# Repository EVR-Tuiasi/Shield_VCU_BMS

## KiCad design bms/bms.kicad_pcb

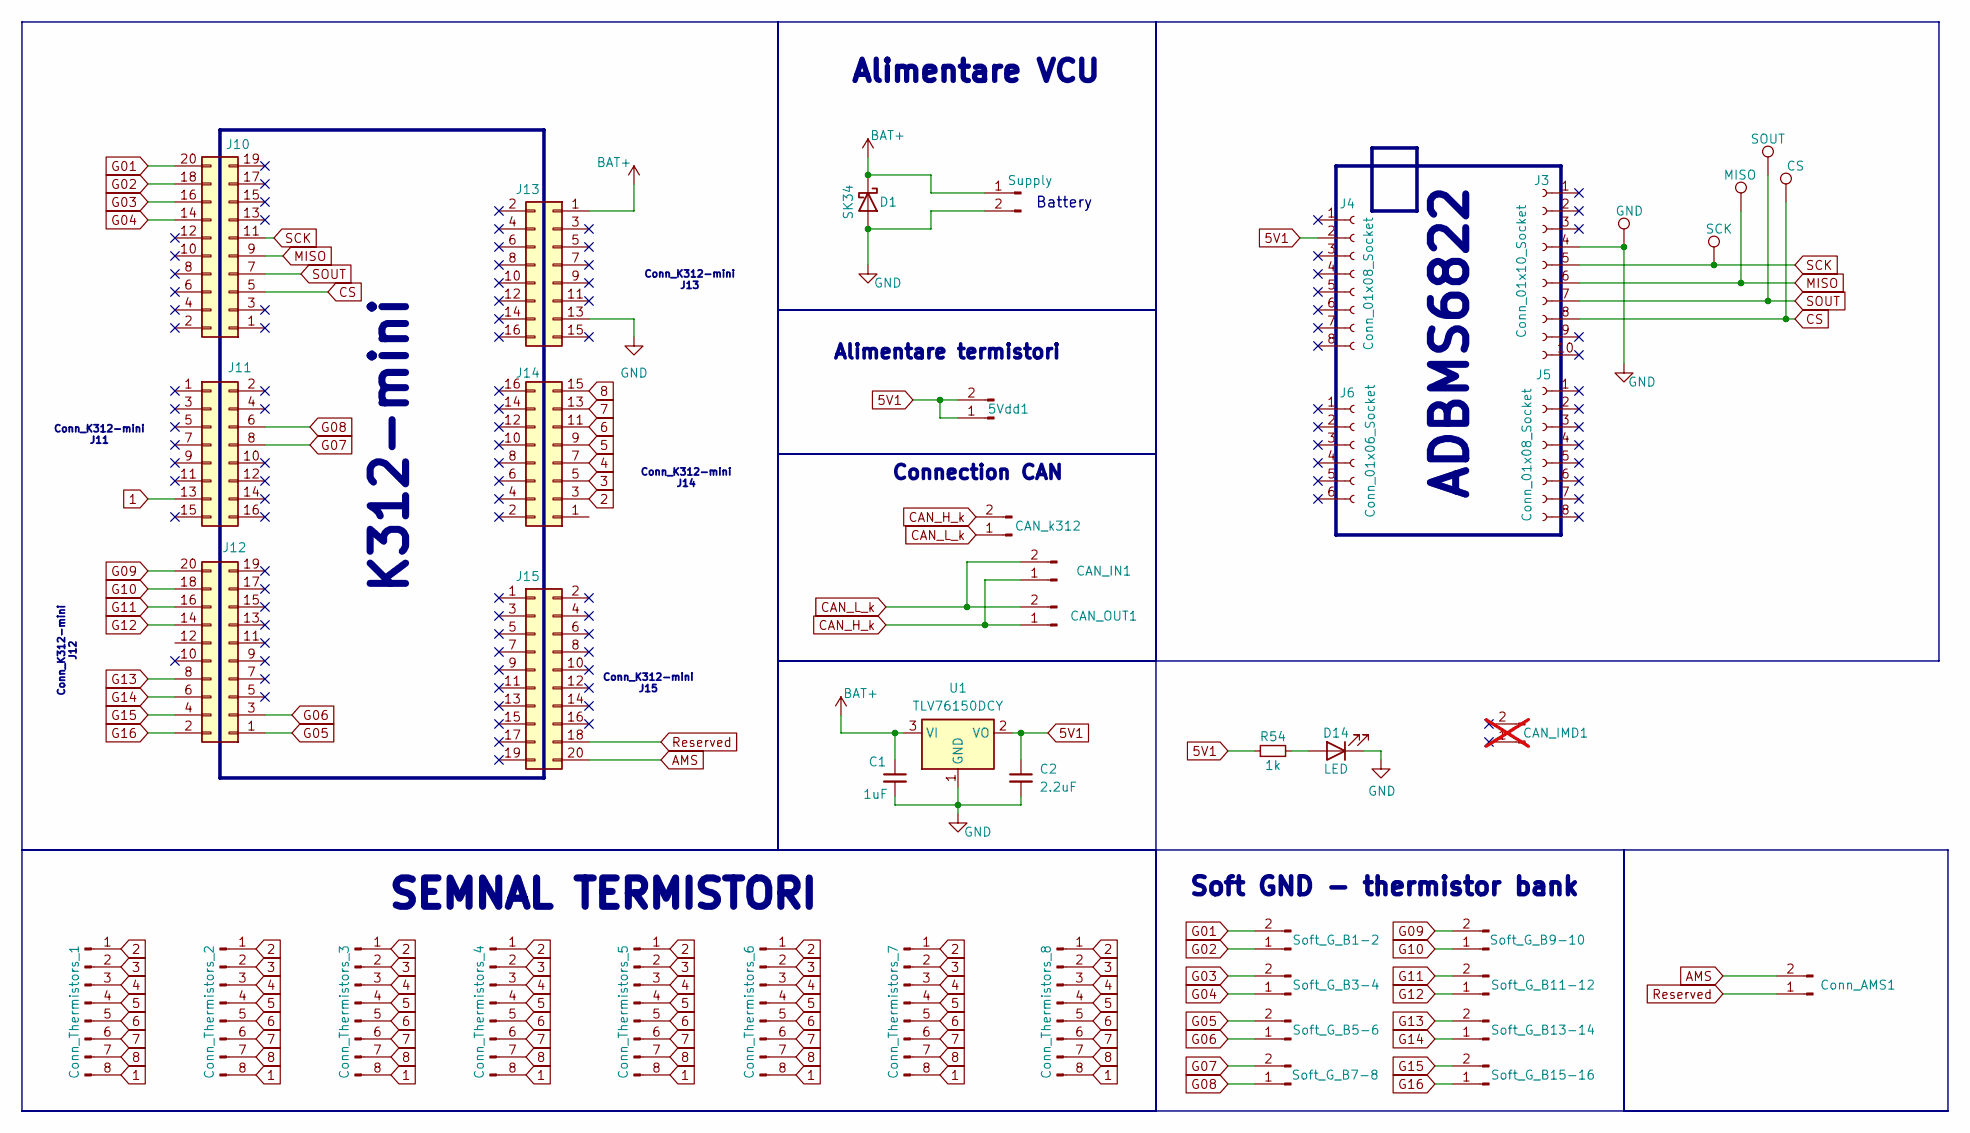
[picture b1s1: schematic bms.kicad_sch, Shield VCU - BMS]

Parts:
5Vdd1: Conn_01x02_Pin; JST_EH_B2B-EH-A_1x02_P2.50mm_Vertical
B1: Supply; JST_EH_B2B-EH-A_1x02_P2.50mm_Vertical
C1: 1uF; C_0805_2012Metric_Pad1.18x1.45mm_HandSolder
C2: 2.2uF; C_0805_2012Metric_Pad1.18x1.45mm_HandSolder
CAN_IMD1: Conn_01x02_Pin; not fitted
CAN_IN1: Conn_01x02_Pin; JST_PH_B2B-PH-K_1x02_P2.00mm_Vertical
CAN_OUT1: Conn_01x02_Pin; JST_PH_B2B-PH-K_1x02_P2.00mm_Vertical
CAN_k312: Conn_01x02_Pin; PinHeader_1x02_P2.54mm_Vertical
CS1: CS; TestPoint_Loop_D2.50mm_Drill1.0mm
Conn_AMS1: Conn_01x02_Pin; JST_EH_B2B-EH-A_1x02_P2.50mm_Vertical
Conn_Thermistors_1, Conn_Thermistors_2, Conn_Thermistors_3, Conn_Thermistors_4, Conn_Thermistors_5, Conn_Thermistors_6, Conn_Thermistors_7, Conn_Thermistors_8: Conn_01x08_Pin; JST_EH_B8B-EH-A_1x08_P2.50mm_Vertical
D1: SK34; D_SMA_Handsoldering
D14: LED; LED_0805_2012Metric
GND1: GND; TestPoint_Loop_D2.50mm_Drill1.0mm
J3: Conn_01x10_Socket; PinSocket_1x10_P2.54mm_Vertical
J4, J5: Conn_01x08_Socket; PinSocket_1x08_P2.54mm_Vertical
J6: Conn_01x06_Socket; PinSocket_1x06_P2.54mm_Vertical
J10, J12, J15: Conn_02x10_Odd_Even; PinHeader_2x10_P2.54mm_Vertical
J11, J13, J14: Conn_02x08_Odd_Even; PinHeader_2x08_P2.54mm_Vertical
MISO1: MISO; TestPoint_Loop_D2.50mm_Drill1.0mm
R54: 1k; R_1206_3216Metric_Pad1.30x1.75mm_HandSolder
SCK1: SCK; TestPoint_Loop_D2.50mm_Drill1.0mm
SOUT1: SOUT; TestPoint_Loop_D2.50mm_Drill1.0mm
Soft_G_B1-2, Soft_G_B3-4, Soft_G_B5-6, Soft_G_B7-8, Soft_G_B9-10, Soft_G_B11-12, Soft_G_B13-14, Soft_G_B15-16: Conn_01x02_Pin; JST_EH_B2B-EH-A_1x02_P2.50mm_Vertical
U1: TLV76150DCY; SOT-223-3_TabPin2

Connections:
1: Conn_Thermistors_1.8, Conn_Thermistors_2.8, Conn_Thermistors_3.8, Conn_Thermistors_4.8, Conn_Thermistors_5.8, Conn_Thermistors_6.8, Conn_Thermistors_7.8, Conn_Thermistors_8.8, J11.13
2: Conn_Thermistors_1.1, Conn_Thermistors_2.1, Conn_Thermistors_3.1, Conn_Thermistors_4.1, Conn_Thermistors_5.1, Conn_Thermistors_6.1, Conn_Thermistors_7.1, Conn_Thermistors_8.1, J14.3
3: Conn_Thermistors_1.2, Conn_Thermistors_2.2, Conn_Thermistors_3.2, Conn_Thermistors_4.2, Conn_Thermistors_5.2, Conn_Thermistors_6.2, Conn_Thermistors_7.2, Conn_Thermistors_8.2, J14.5
4: Conn_Thermistors_1.3, Conn_Thermistors_2.3, Conn_Thermistors_3.3, Conn_Thermistors_4.3, Conn_Thermistors_5.3, Conn_Thermistors_6.3, Conn_Thermistors_7.3, Conn_Thermistors_8.3, J14.7
5: Conn_Thermistors_1.4, Conn_Thermistors_2.4, Conn_Thermistors_3.4, Conn_Thermistors_4.4, Conn_Thermistors_5.4, Conn_Thermistors_6.4, Conn_Thermistors_7.4, Conn_Thermistors_8.4, J14.9
5V1: 5Vdd1.1, 5Vdd1.2, C2.1, J4.2 (Pin_2_2), R54.1, U1.2 (VO)
6: Conn_Thermistors_1.5, Conn_Thermistors_2.5, Conn_Thermistors_3.5, Conn_Thermistors_4.5, Conn_Thermistors_5.5, Conn_Thermistors_6.5, Conn_Thermistors_7.5, Conn_Thermistors_8.5, J14.11
7: Conn_Thermistors_1.6, Conn_Thermistors_2.6, Conn_Thermistors_3.6, Conn_Thermistors_4.6, Conn_Thermistors_5.6, Conn_Thermistors_6.6, Conn_Thermistors_7.6, Conn_Thermistors_8.6, J14.13
8: Conn_Thermistors_1.7, Conn_Thermistors_2.7, Conn_Thermistors_3.7, Conn_Thermistors_4.7, Conn_Thermistors_5.7, Conn_Thermistors_6.7, Conn_Thermistors_7.7, Conn_Thermistors_8.7, J14.15
AMS: Conn_AMS1.2, J15.20
BAT+: B1.1, C1.1, D1.1 (K), J13.1, U1.3 (VI)
CAN_H_k: CAN_IN1.1, CAN_OUT1.1, CAN_k312.2
CAN_L_k: CAN_IN1.2, CAN_OUT1.2, CAN_k312.1
CS: CS1.1 (1_1), J3.8, J10.5
G01: J10.20, Soft_G_B1-2.2
G02: J10.18, Soft_G_B1-2.1
G03: J10.16, Soft_G_B3-4.2
G04: J10.14, Soft_G_B3-4.1
G05: J12.1, Soft_G_B5-6.2
G06: J12.3, Soft_G_B5-6.1
G07: J11.8, Soft_G_B7-8.2
G08: J11.6, Soft_G_B7-8.1
G09: J12.20, Soft_G_B9-10.2
G10: J12.18, Soft_G_B9-10.1
G11: J12.16, Soft_G_B11-12.2
G12: J12.14, Soft_G_B11-12.1
G13: J12.8, Soft_G_B13-14.2
G14: J12.6, Soft_G_B13-14.1
G15: J12.4, Soft_G_B15-16.2
G16: J12.2, Soft_G_B15-16.1
GND: B1.2, C1.2, C2.2, D1.2 (A), D14.1 (K), GND1.1 (1_1), J3.4, J13.13, U1.1 (GND)
MISO: J3.6, J10.9, MISO1.1 (1_1)
unnamed: D14.2 (A), R54.2
Reserved: Conn_AMS1.1, J15.18
SCK: J3.5, J10.11, SCK1.1 (1_1)
SOUT: J3.7, J10.7, SOUT1.1 (1_1)

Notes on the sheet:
K312-mini
SEMNAL TERMISTORI
Soft GND - thermistor bank
Conn_K312-mini J13
Battery
Alimentare VCU
Conn_K312-mini J14
Conn_K312-mini J15
Conn_K312-mini J12
ADBMS6822
Connection CAN
Alimentare termistori
Conn_K312-mini J11

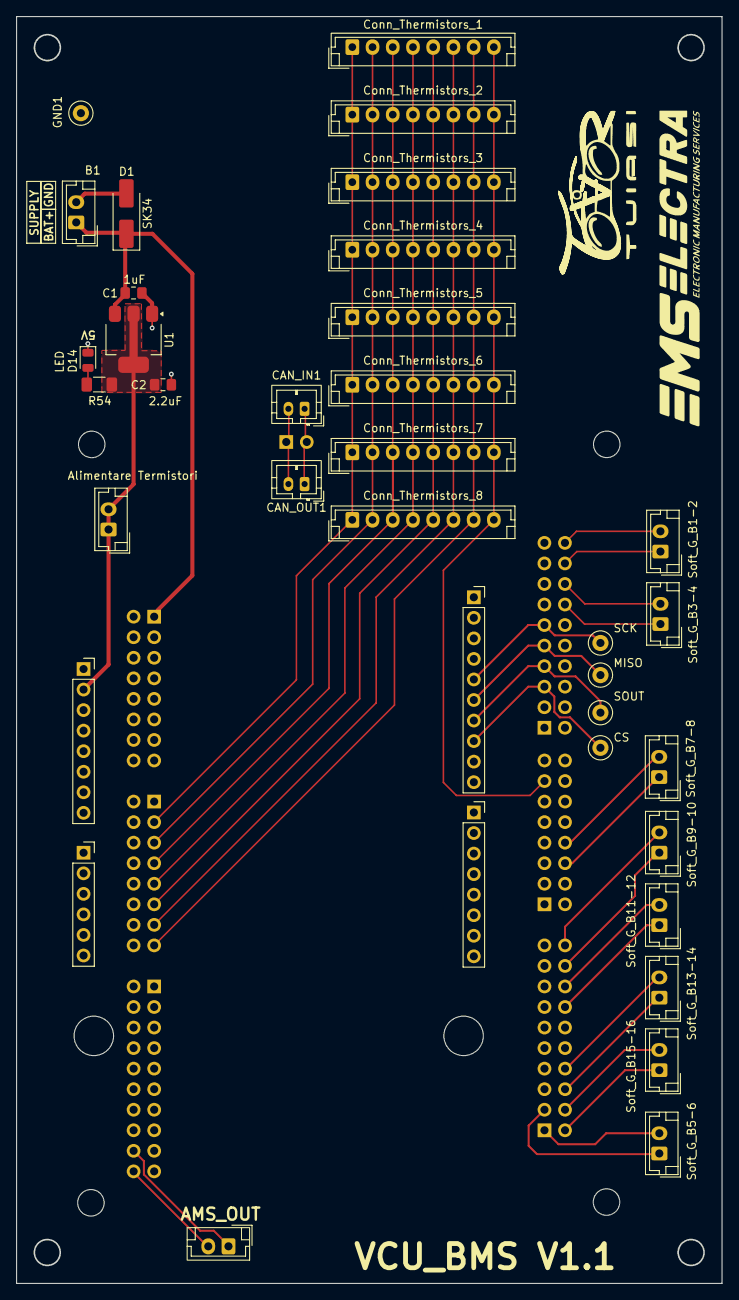
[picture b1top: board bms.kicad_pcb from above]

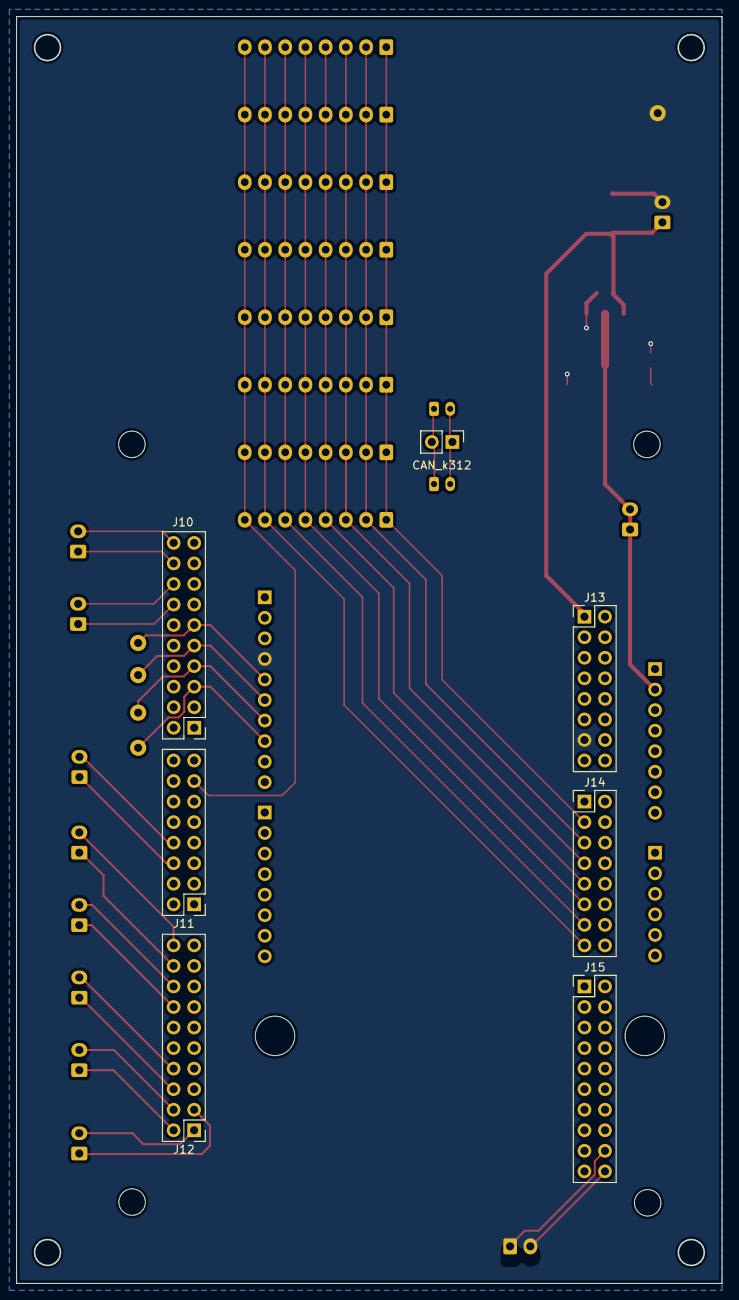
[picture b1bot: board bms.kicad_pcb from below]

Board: 2 copper layers, 87.1 x 156.5 mm, 43 parts (7 on the bottom side), 36 nets.

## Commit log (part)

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2026-03-27 Prajeala
2026-03-27 prajeal2
2026-03-27 prajeala_maxima_3
2026-03-29 idee de pcb bms
2026-03-29 fara program deschis
2026-03-29 v0.99
2026-03-30 V0.999 a little more polished
2026-03-31 inca un update
2026-05-01 Check on layout+block diagram
    4x mounting holes with GND connection - added;
    PCB size small increaze
    block diagram reshaped
2026-05-11 added datasheets and revised layout to be continued
2026-05-12 PCB modified - lange update
2026-05-12 1x GND plane now removed
2026-05-14 STEP file added
2026-05-26 Revision / date added
2026-06-15 CAN_IN & CAN_OUT - added
2026-06-21 Moved components on front size for better ground plane
2026-06-25 Routed all signals over GND planes
2026-06-29 GBR added + sent
